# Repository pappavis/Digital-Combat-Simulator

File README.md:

# Digital-Combat-Simulator
Afrikaans: Cockpit Panels en printplate vir DCS World door Michiel Erasmus <br/>
ENG: This is the main powerpanel design for flightsimulator DCS: MiG-21bis.

Requiremens:
---
KiCAD to view the files: http://kicad.org <br/>
FlatCAM to generate GERBERs: http://flatcam.org<br/>
<br/>
3D render<br/>
<br/>

Credits
---
**Contact** Michiel Erasmus <br/>
**e-Mail** thebapodcast@gmail.com<br/>
**Created** 12-2-2016<br/>

<br/>
Arduino Modulaire cockpit panel for the DCS: MiG-21bis by Eagle Dynamics &amp; Leatherneck Software<br/>

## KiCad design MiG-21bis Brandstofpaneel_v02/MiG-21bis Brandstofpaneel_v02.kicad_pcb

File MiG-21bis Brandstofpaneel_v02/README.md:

<br/>
MiG-21bis Main PowerPanel V2.0<br/>
<br/>
<br/>
door Michiel Erasmus.

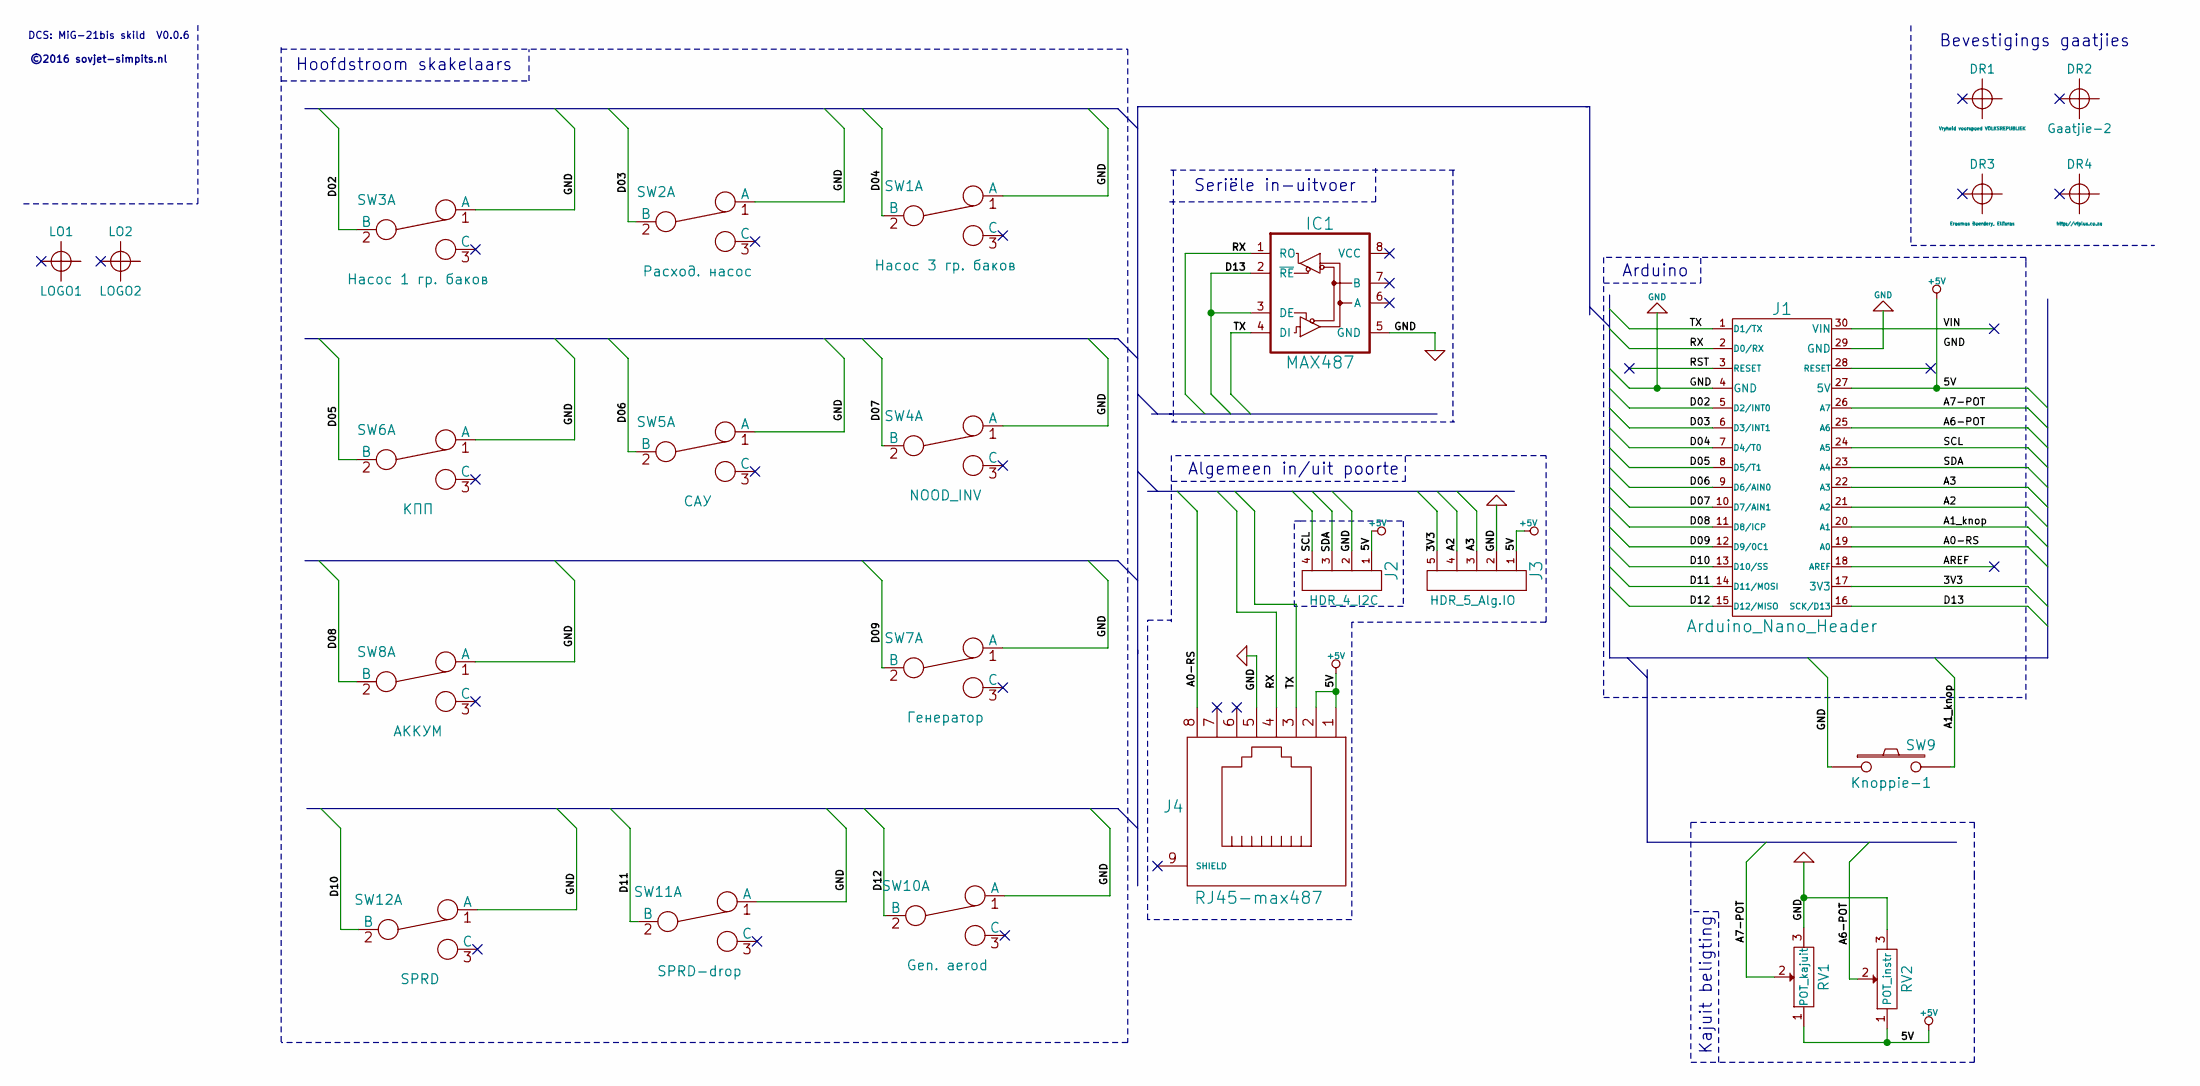
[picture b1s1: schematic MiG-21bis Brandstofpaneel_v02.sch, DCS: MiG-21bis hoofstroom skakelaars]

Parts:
DR1: Vryheid voorspoed VOLKSREPUBLIEK; MountingHole_4mm
DR2: Gaatjie-2; MountingHole_4mm
DR3: Erasmus Boerdery, Ellisras; MountingHole_4mm
DR4: http://vfplus.co.za; MountingHole_4mm
IC1: MAX487; dil_8-300
J1: Arduino_Nano_Header
J2: HDR_4_I2C; Pin_Header_Straight_1x04
J3: HDR_5_Alg.IO; TerminalBlock_Pheonix_PT-3.5mm_5pol
J4: RJ45-max487; RJ45_8
LO1: LOGO1; Logo_silk_OSHW_12x13mm
LO2: LOGO2; LOGO-sovjetSimpits
RV1: POT_kajuit; Potentiometer_Alps-RK163-single_15mm
RV2: POT_instr; Potentiometer_Alps-RK163-single_15mm
SW1: Насос 3 гр. баков; switch_100sp5
SW2: Расход. насос; switch_100sp5
SW3: Насос 1 гр. баков; switch_100sp5
SW4: NOOD_INV; switch_100sp5
SW5: САУ; switch_100sp5
SW6: KПП; switch_100sp5
SW7: Генератор; switch_100sp5
SW8: АККУМ; switch_100sp5
SW9: Knoppie-1; PCB_PUSH
SW10: Gen. aerod; switch_100sp5
SW11: SPRD-drop; switch_100sp5
SW12: SPRD; switch_100sp5

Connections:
+5V: J1.27 (5V), J2.1, J3.1, J4.1, J4.2, RV1.1, RV2.1
/3V3: J1.17 (3V3), J3.5
/A0-RS: J1.19 (A0), J4.8
/A1_knop: J1.20 (A1), SW9.2
/A2: J1.21 (A2), J3.4
/A3: J1.22 (A3), J3.3
/A6-POT: J1.25 (A6), RV2.2
/A7-POT: J1.26 (A7), RV1.2
/AREF: J1.18 (AREF)
/D02: J1.5 (D2/INT0), SW3.2 (B)
/D03: J1.6 (D3/INT1), SW2.2 (B)
/D04: J1.7 (D4/T0), SW1.2 (B)
/D05: J1.8 (D5/T1), SW6.2 (B)
/D06: J1.9 (D6/AIN0), SW5.2 (B)
/D07: J1.10 (D7/AIN1), SW4.2 (B)
/D08: J1.11 (D8/ICP), SW8.2 (B)
/D09: J1.12 (D9/0C1), SW7.2 (B)
/D10: J1.13 (D10/SS), SW12.2 (B)
/D11: J1.14 (D11/MOSI), SW11.2 (B)
/D12: J1.15 (D12/MISO), SW10.2 (B)
/D13: IC1.2 (~RE), IC1.3 (DE), J1.16 (SCK/D13)
/RST: J1.3 (RESET)
/RX: IC1.1 (RO), J1.2 (D0/RX), J4.4
/SCL: J1.24 (A5), J2.4
/SDA: J1.23 (A4), J2.3
/TX: IC1.4 (DI), J1.1 (D1/TX), J4.3
/VIN: J1.30 (VIN)
GND: IC1.5 (GND), J1.4 (GND), J1.29 (GND), J2.2, J3.2, J4.5, RV1.3, RV2.3, SW1.1 (A), SW2.1 (A), SW3.1 (A), SW4.1 (A), SW5.1 (A), SW6.1 (A), SW7.1 (A), SW8.1 (A), SW9.1, SW10.1 (A), SW11.1 (A), SW12.1 (A)

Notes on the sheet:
Bevestigings gaatjies
DCS: MiG-21bis skild V0.0.6
©2016 sovjet-simpits.nl
Kajuit beligting
Seriële in-uitvoer
Arduino
Hoofdstroom skakelaars
Algemeen in/uit poorte

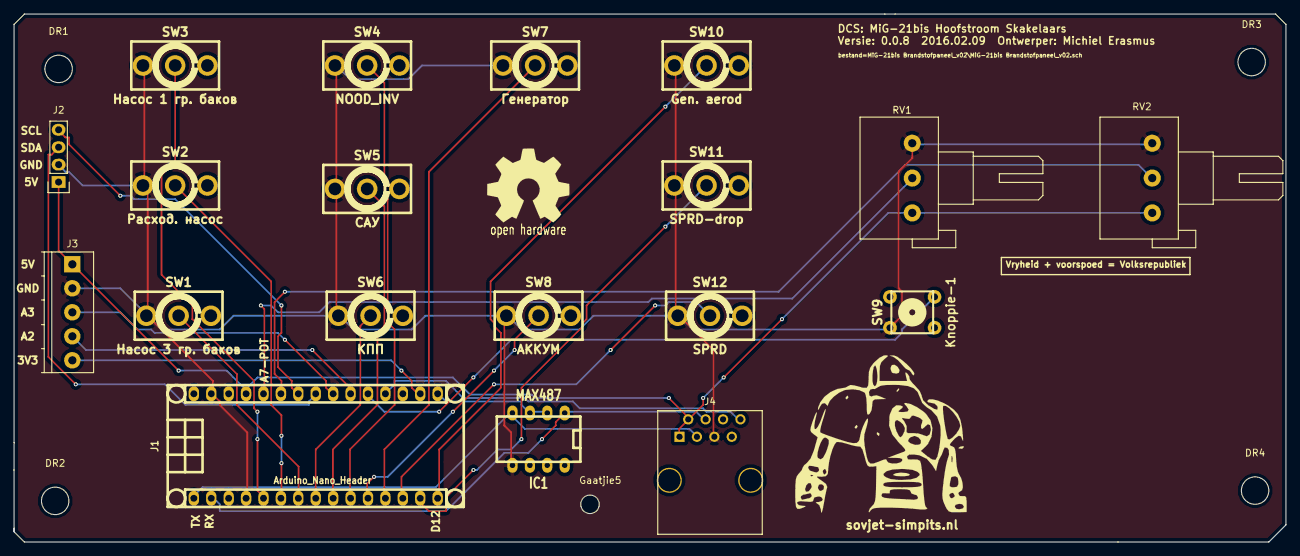
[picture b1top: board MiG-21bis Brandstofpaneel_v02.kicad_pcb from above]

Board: 2 copper layers, 185.5 x 77.0 mm, 26 parts (0 on the bottom side), 25 nets.

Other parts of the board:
Gaatjie5: MountingHole_2-7mm

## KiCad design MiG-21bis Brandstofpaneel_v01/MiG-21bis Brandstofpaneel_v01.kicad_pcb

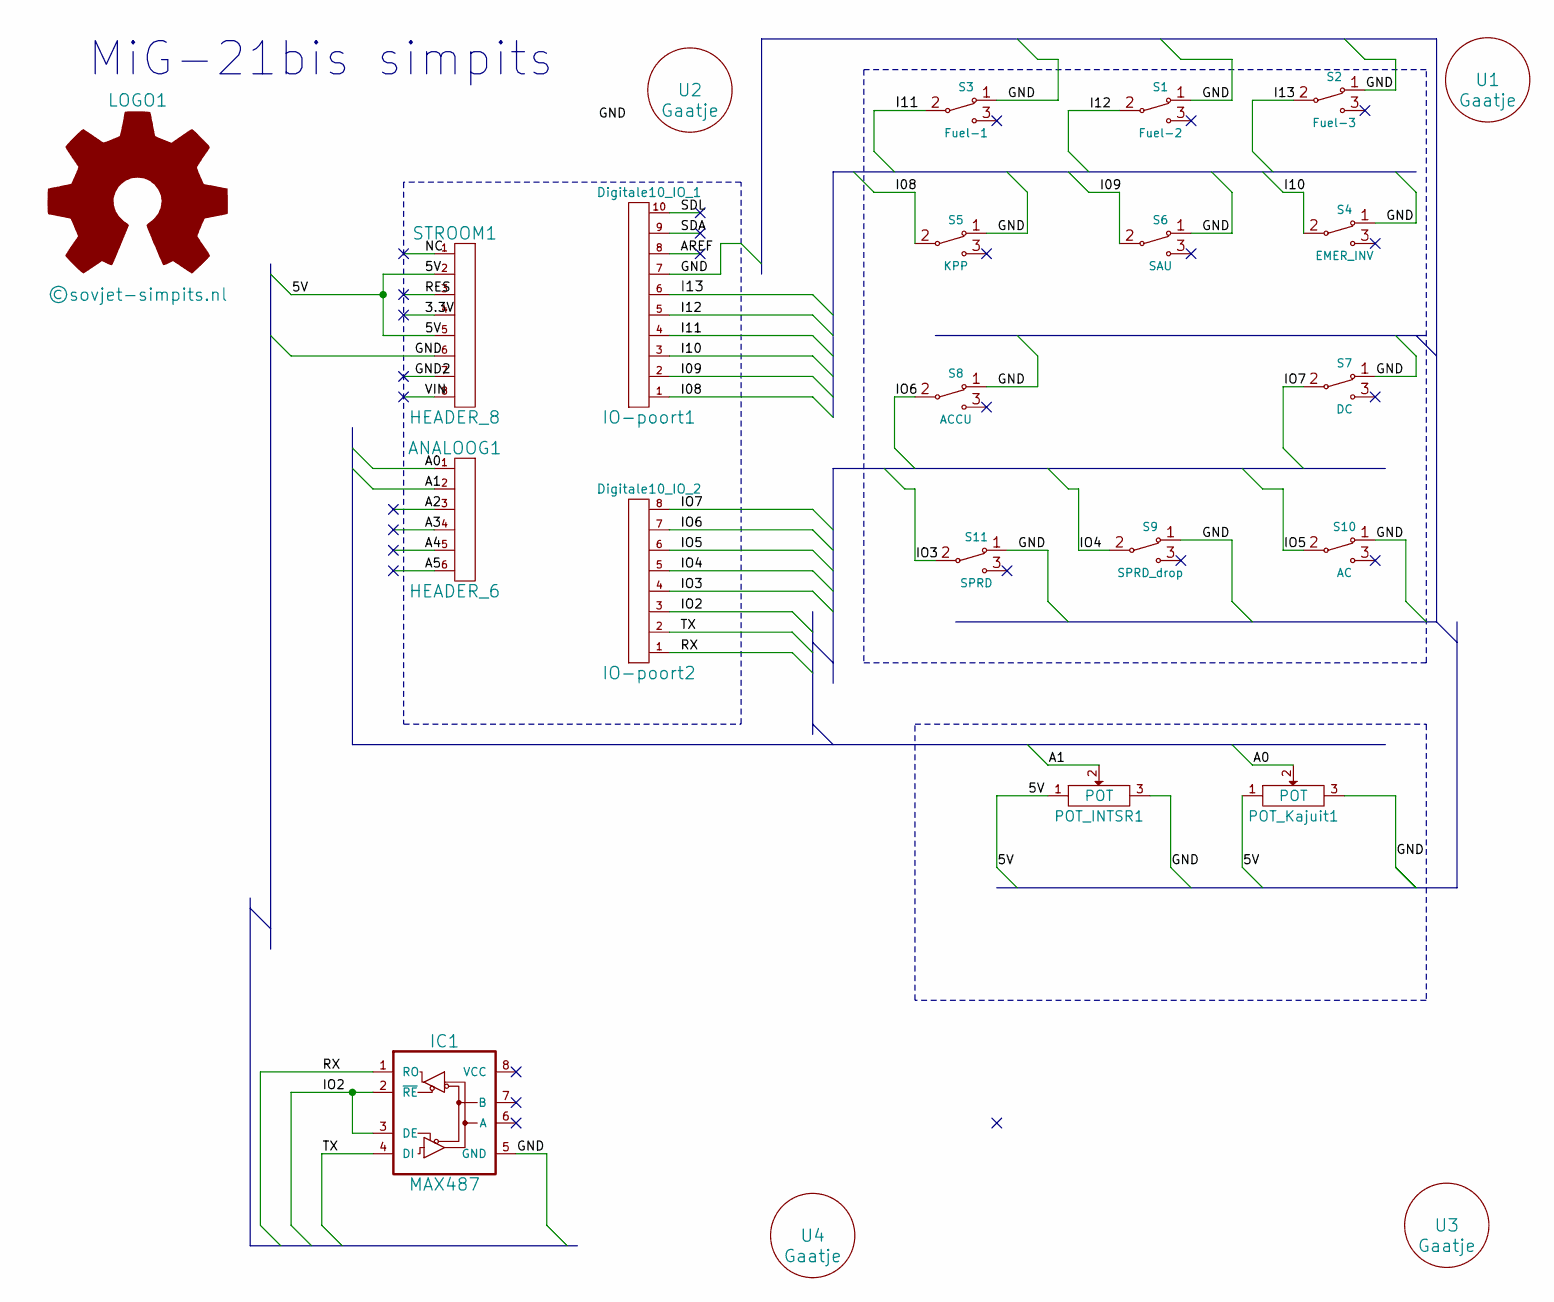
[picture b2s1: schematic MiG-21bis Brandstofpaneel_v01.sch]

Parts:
ANALOOG1: HEADER_6; TerminalBlock_Pheonix_MPT-2.54mm_6pol
IC1: MAX487; dil_8-300
IO-poort1: Digitale10_IO_1; TerminalBlock_Pheonix_MPT-2.54mm_10pol
IO-poort2: Digitale10_IO_2; TerminalBlock_Pheonix_MPT-2.54mm_10pol
LOGO1: ©sovjet-simpits.nl; Logo_copper_OSHW_12x13mm
POT_INTSR1: POT; Potentiometer_WirePads_largePads
POT_Kajuit1: POT; Potentiometer_WirePads_largePads
S1: Fuel-2; switch_100sp5
S2: Fuel-3; switch_100sp5
S3: Fuel-1; switch_100sp5
S4: EMER_INV; switch_100sp5
S5: KPP; switch_100sp5
S6: SAU; switch_100sp5
S7: DC; switch_100sp5
S8: ACCU; switch_100sp5
S9: SPRD_drop; switch_100sp5
S10: AC; switch_100sp5
S11: SPRD; switch_100sp5
STROOM1: HEADER_8; TerminalBlock_Pheonix_PT-3.5mm_8pol
U1, U2, U3, U4: Gaatje; hole_5mm

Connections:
/3.3V: STROOM1.4
/5V: POT_INTSR1.1, POT_Kajuit1.1, STROOM1.2, STROOM1.5
/A0: ANALOOG1.1, POT_Kajuit1.2
/A1: ANALOOG1.2, POT_INTSR1.2
/A2: ANALOOG1.3
/A3: ANALOOG1.4
/A4: ANALOOG1.5
/A5: ANALOOG1.6
/AREF: IO-poort1.8
/GND2: STROOM1.7
/I08: IO-poort1.1, S5.2
/I09: IO-poort1.2, S6.2
/I10: IO-poort1.3, S4.2
/I11: IO-poort1.4, S3.2
/I12: IO-poort1.5, S1.2
/I13: IO-poort1.6, S2.2
/IO2: IC1.2 (~RE), IC1.3 (DE), IO-poort2.3
/IO3: IO-poort2.4, S11.2
/IO4: IO-poort2.5, S9.2
/IO5: IO-poort2.6, S10.2
/IO6: IO-poort2.7, S8.2
/IO7: IO-poort2.8, S7.2
/NC: STROOM1.1
/RES: STROOM1.3
/RX: IC1.1 (RO), IO-poort2.1
/SDA: IO-poort1.9
/SDL: IO-poort1.10
/TX: IC1.4 (DI), IO-poort2.2
/VIN: STROOM1.8

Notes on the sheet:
MiG-21bis simpits

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
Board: 2 copper layers, 23 parts (0 on the bottom side), 18 nets, no tracks yet.

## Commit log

2017-10-13 Eerste commit op 14-10-2017
2017-10-19 plaatje toegevoegd
2021-11-10 Update README.md
    https://forum.kicad.info/t/warning-avoid-all-links-to-kicad-pcb-org-use-kicad-org/31521
